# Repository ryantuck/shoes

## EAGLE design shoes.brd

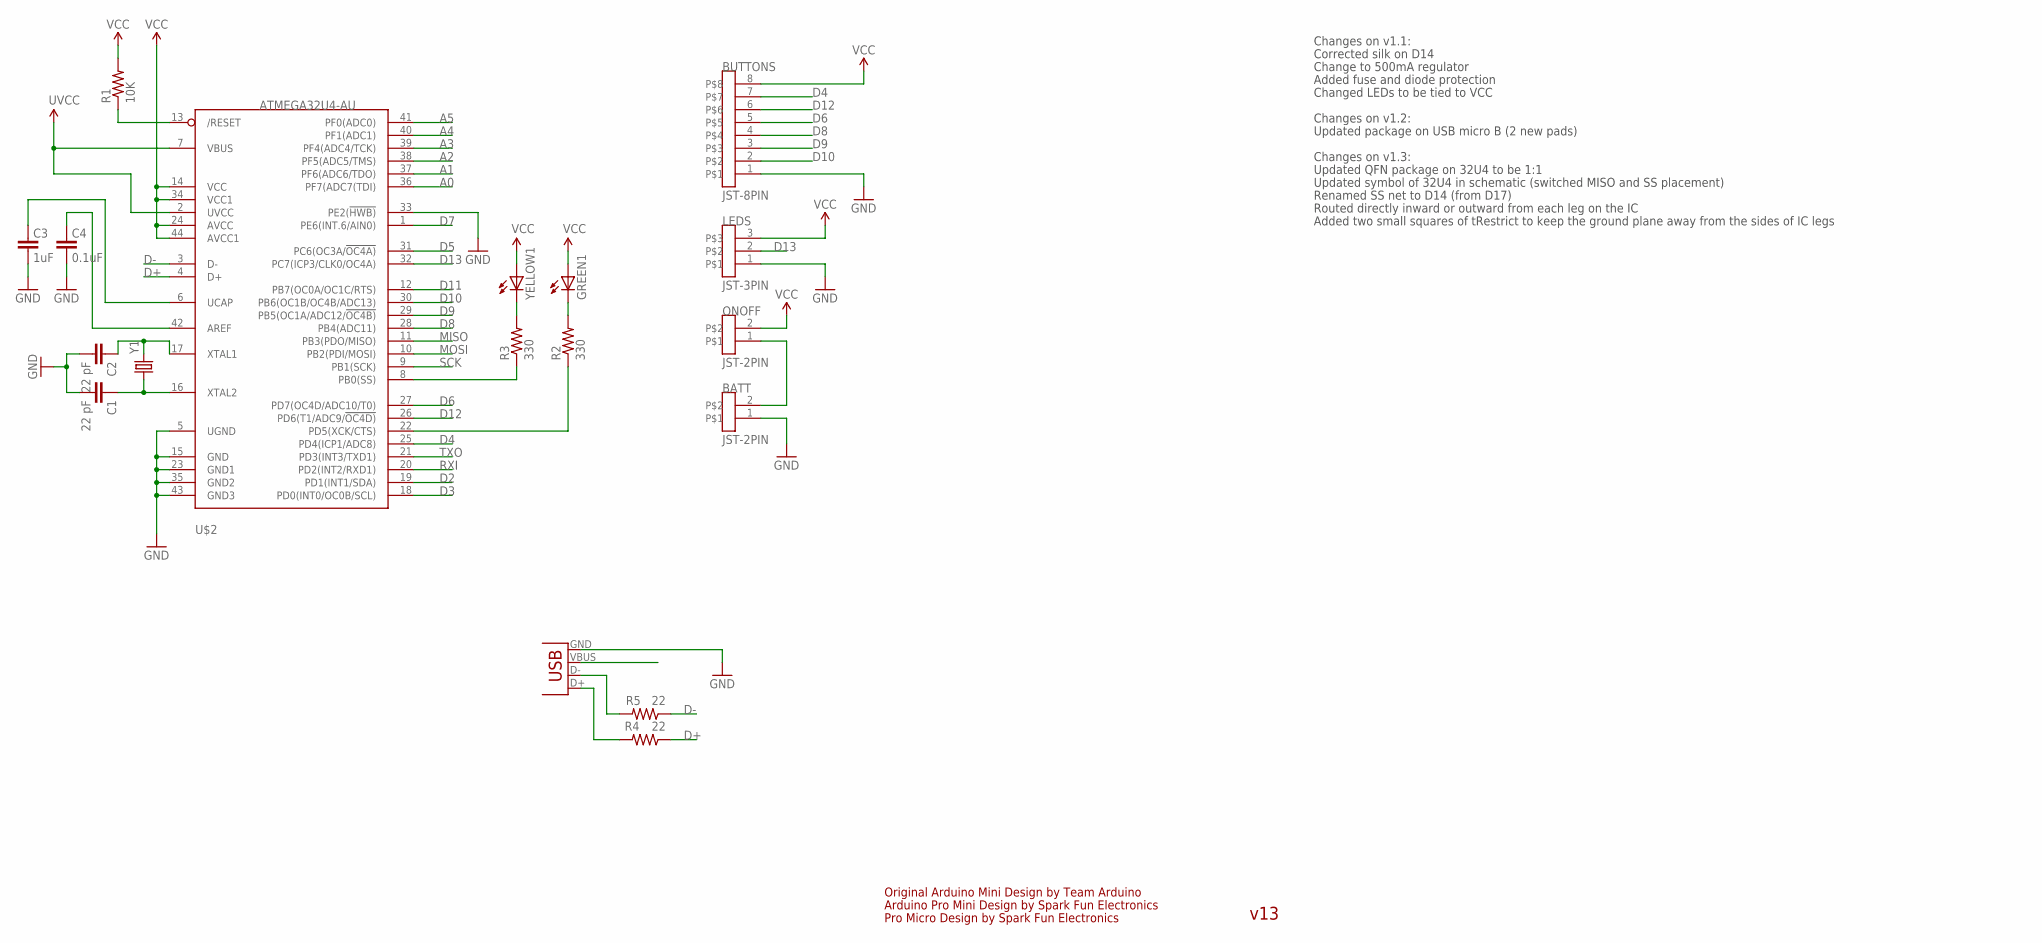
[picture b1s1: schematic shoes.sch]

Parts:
BATT: JST-2PIN; JST-PH-2
BUTTONS: JST-8PIN; JST-PH-8
C1, C2: 22 pF; 0805
C3: 1uF; 0805
C4: 0.1uF; 0805
GREEN1: LED; 0805_P
LEDS: JST-3PIN; JST-PH-3
ONOFF: JST-2PIN; JST-PH-2
R1: 10K; 0805
R2, R3: 330; 0805
R4, R5: 22; 0805
U$2: ATMEGA32U4-AU; TQFP44
X2: USB-MICROB
Y1: CRYSTALHC49US; HC49US
YELLOW1: LED; 0805_P

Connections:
5V: BUTTONS.8, GREEN1.NEG (A), LEDS.3, ONOFF.2, R1.2, U$2.14 (VCC), U$2.24 (AVCC), U$2.34 (VCC1), U$2.44 (AVCC1), YELLOW1.NEG (A)
A0: U$2.36 (PF7(ADC7(TDI))
A1: U$2.37 (PF6(ADC6/TDO))
A2: U$2.38 (PF5(ADC5/TMS))
A3: U$2.39 (PF4(ADC4/TCK))
A4: U$2.40 (PF1(ADC1))
A5: U$2.41 (PF0(ADC0))
D2: U$2.19 (PD1(INT1/SDA))
D3: U$2.18 (PD0(INT0/OC0B/SCL))
D4: BUTTONS.7, U$2.25 (PD4(ICP1/ADC8))
D5: U$2.31 (PC6(OC3A/!OC4A))
D6: BUTTONS.5, U$2.27 (PD7(OC4D/ADC10/T0))
D7: U$2.1 (PE6(INT.6/AIN0))
D8: BUTTONS.4, U$2.28 (PB4(ADC11))
D9: BUTTONS.3, U$2.29 (PB5(OC1A/ADC12/!OC4B))
D10: BUTTONS.2, U$2.30 (PB6(OC1B/OC4B/ADC13))
D11: U$2.12 (PB7(OC0A/OC1C/RTS))
D12: BUTTONS.6, U$2.26 (PD6(T1/ADC9/!OC4D))
D13: LEDS.2, U$2.32 (PC7(ICP3/CLK0/OC4A))
D14: R3.1, U$2.8 (PB0(SS))
D+: R4.1, U$2.4 (D+)
D-: R5.1, U$2.3 (D-)
GND: BATT.1, BUTTONS.1, C1.POS (2), C2.POS (2), C3.1, C4.1, LEDS.1, U$2.5 (UGND), U$2.15 (GND), U$2.23 (GND1), U$2.33 (PE2(!HWB)), U$2.35 (GND2), U$2.43 (GND3), X2.GND
MISO: U$2.11 (PB3(PDO/MISO))
MOSI: U$2.10 (PB2(PDI/MOSI))
unnamed: C2.NEG (1), U$2.17 (XTAL1), Y1.2
unnamed: R4.2, X2.D+
unnamed: R5.2, X2.D-
unnamed: C1.NEG (1), U$2.16 (XTAL2), Y1.1
unnamed: C4.2, U$2.42 (AREF)
unnamed: C3.2, U$2.6 (UCAP)
unnamed: R3.2, YELLOW1.POS (C)
unnamed: GREEN1.POS (C), R2.2
RESET1: R1.1, U$2.13 (/RESET)
RXI: U$2.20 (PD2(INT2/RXD1))
SCK: U$2.9 (PB1(SCK))
TXLED: R2.1, U$2.22 (PD5(XCK/CTS))
TXO: U$2.21 (PD3(INT3/TXD1))
UVCC: U$2.2 (UVCC), U$2.7 (VBUS), X2.VBUS
VIN: BATT.2, ONOFF.1

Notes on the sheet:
Original Arduino Mini Design by Team Arduino
Arduino Pro Mini Design by Spark Fun Electronics
Pro Micro Design by Spark Fun Electronics
Changes on v1.1:
Corrected silk on D14
Change to 500mA regulator
Added fuse and diode protection
Changed LEDs to be tied to VCC
Changes on v1.2:
Updated package on USB micro B (2 new pads)
Changes on v1.3:
Updated QFN package on 32U4 to be 1:1
Updated symbol of 32U4 in schematic (switched MISO and SS placement)
Renamed SS net to D14 (from D17)
Routed directly inward or outward from each leg on the IC
Added two small squares of tRestrict to keep the ground plane away from the sides of IC legs
v13

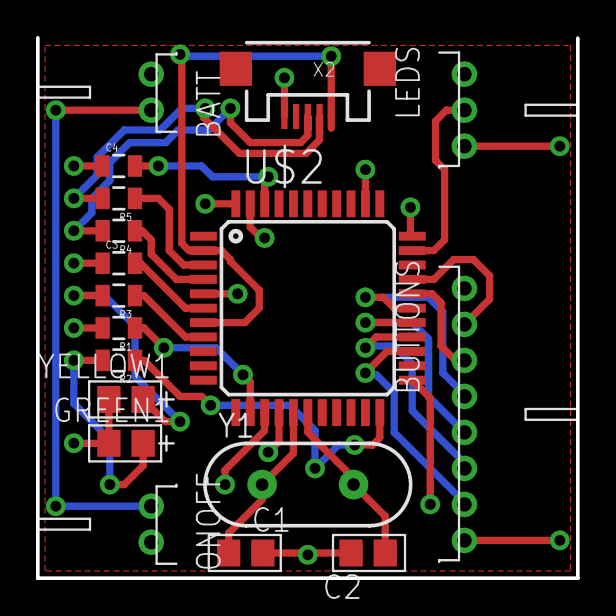
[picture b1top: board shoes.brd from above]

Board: 2 copper layers, 30.0 x 30.0 mm, 18 parts (0 on the bottom side), 24 nets.

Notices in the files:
parts and their libraries:
SparkFun-Connectors: Licensing: CC v3.0 Share-Alike You are welcome to use this library for commercial purposes.
